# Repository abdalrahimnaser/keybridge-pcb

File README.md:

Get yourself a premade KeyBridge here: https://localdevices.net/products/keybridge

Link to the software repo: https://github.com/abdalrahimnaser/keybridge-esphome

## License
This hardware design is licensed under [CC BY-NC-SA 4.0](https://creativecommons.org/licenses/by-nc-sa/4.0/). 
You are free to build and modify it for personal, non-commercial use. Commercial manufacturing and sales are prohibited without prior written permission.

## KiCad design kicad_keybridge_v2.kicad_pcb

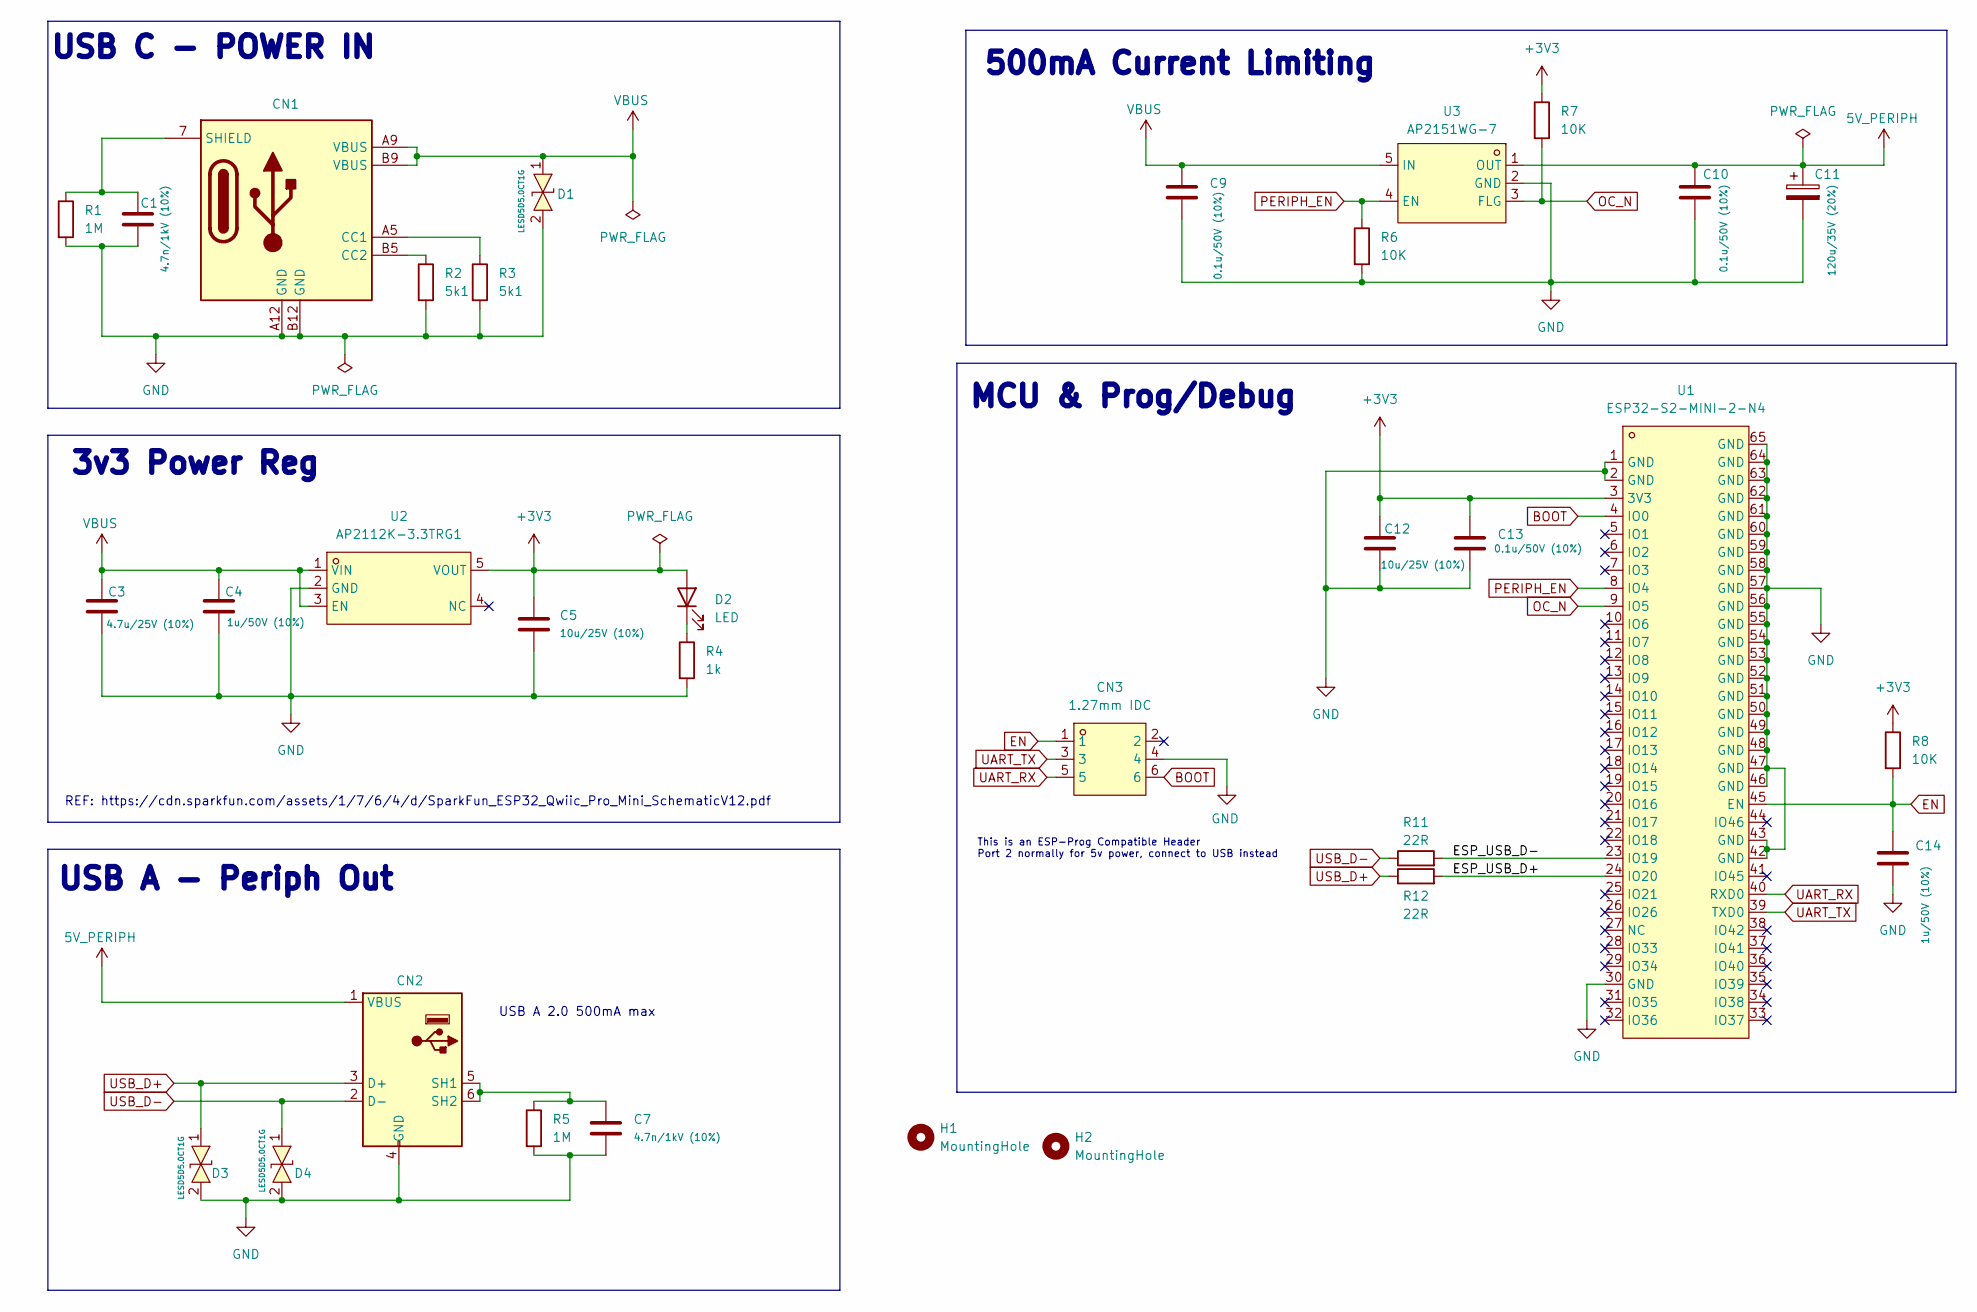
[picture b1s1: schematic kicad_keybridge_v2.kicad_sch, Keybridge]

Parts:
C1, C7: 4.7n/1kV (10%); C_1206_3216Metric; LCSC C107198
C3: 4.7u/25V (10%); C_0805_2012Metric; LCSC C98195
C4, C14: 1u/50V (10%); C_0805_2012Metric; LCSC C28323
C5, C12: 10u/25V (10%); C_0805_2012Metric; LCSC C15850
C9, C10, C13: 0.1u/50V (10%); C_0805_2012Metric; LCSC C1711
C11: 120u/35V (20%); CP_Elec_6.3x7.7; LCSC C49256854
CN1: USB-TYPE-C-6P_Power; TYPE-C-SMD_TYPE-C-6P; MPN USB-TYPE-C-009; LCSC Part C2927029
CN2: AF180QT1.0; USB-A-SMD_AF180QT1.0; MPN AF180QT1.0; LCSC Part C404963
CN3: 1.27mm IDC; CONN-SMD_6P-P1.27-LS5.8; MPN HX JN1.27-2x3 TP H4.9; LCSC Part C42372553
D1, D3, D4: LESD5D5.0CT1G; SOD-523_L1.2-W0.8-LS1.6-BI; MPN LESD5D5.0CT1G; LCSC Part C5246195
D2: LED; LED_0805_2012Metric_Pad1.15x1.40mm_HandSolder; LCSC C2297
H1, H2: MountingHole; MountingHole_2.2mm_M2
R1, R5: 1M; R_0603_1608Metric_Pad0.98x0.95mm_HandSolder; LCSC C2907003
R2, R3: 5k1; R_0603_1608Metric_Pad0.98x0.95mm_HandSolder; LCSC C2907044
R4: 1k; R_0603_1608Metric_Pad0.98x0.95mm_HandSolder; LCSC C2907002
R6, R7, R8: 10K; R_0603_1608Metric_Pad0.98x0.95mm_HandSolder; LCSC C844918
R11, R12: 22R; R_0603_1608Metric_Pad0.98x0.95mm_HandSolder; LCSC C107701
U1: ESP32-S2-MINI-2-N4; WIFI-SMD_ESP32-MINI-1-N4; MPN ESP32-S2-MINI-2-N4; LCSC Part C3013906
U2: AP2112K-3.3TRG1; SOT-25-5_L2.9-W1.6-P0.95-LS2.8-BL; MPN AP2112K-3.3TRG1; LCSC Part C51118
U3: AP2151WG-7; SOT-25-5_L3.0-W1.8-P0.95-LS3.0-BR; MPN AP2151WG-7; LCSC Part C110464

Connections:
5V_PERIPH: C10.1, C11.1, CN2.1 (VBUS), U3.1 (OUT)
+3V3: C5.1, C12.1, C13.1, D2.2 (A), R7.1, R8.1, U1.3 (3V3), U2.5 (VOUT)
/ESP_USB_D+: R12.2, U1.24 (IO20)
/ESP_USB_D-: R11.2, U1.23 (IO19)
BOOT: CN3.6, U1.4 (IO0)
EN: C14.1, CN3.1, R8.2, U1.45 (EN)
GND: C1.2, C3.2, C4.2, C5.2, C7.2, C9.2, C10.2, C11.2, C12.2, C13.2, C14.2, CN1.A12 (GND), CN1.B12 (GND), CN2.4 (GND), CN3.4, D1.2, D3.2, D4.2, R1.2, R2.2, R3.2, R4.2, R5.2, R6.2, U1.1 (GND), U1.2 (GND), U1.30 (GND), U1.42 (GND), U1.43 (GND), U1.46 (GND), U1.47 (GND), U1.48 (GND), U1.49 (GND), U1.50 (GND), U1.51 (GND), U1.52 (GND), U1.53 (GND), U1.54 (GND), U1.55 (GND), U1.56 (GND), U1.57 (GND), U1.58 (GND), U1.59 (GND), U1.60 (GND), U1.61 (GND), U1.62 (GND), U1.63 (GND), U1.64 (GND), U1.65 (GND), U2.2 (GND), U3.2 (GND)
unnamed: CN1.A5 (CC1), R3.1
unnamed: CN1.B5 (CC2), R2.1
unnamed: C1.1, CN1.7 (SHIELD), R1.1
unnamed: C7.1, CN2.5 (SH1), CN2.6 (SH2), R5.1
unnamed: D2.1 (K), R4.1
OC_N: R7.2, U1.9 (IO5), U3.3 (FLG)
PERIPH_EN: R6.1, U1.8 (IO4), U3.4 (EN)
UART_RX: CN3.5, U1.40 (RXD0)
UART_TX: CN3.3, U1.39 (TXD0)
USB_D+: CN2.3 (D+), D3.1, R12.1
USB_D-: CN2.2 (D-), D4.1, R11.1
VBUS: C3.1, C4.1, C9.1, CN1.A9 (VBUS), CN1.B9 (VBUS), D1.1, U2.1 (VIN), U2.3 (EN), U3.5 (IN)

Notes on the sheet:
3v3 Power Reg
REF: https://cdn.sparkfun.com/assets/1/7/6/4/d/SparkFun_ESP32_Qwiic_Pro_Mini_SchematicV12.pdf
USB A 2.0 500mA max
USB A - Periph Out
This is an ESP-Prog Compatible Header Port 2 normally for 5v power, connect to USB instead
MCU & Prog/Debug
USB C - POWER IN
500mA Current Limiting

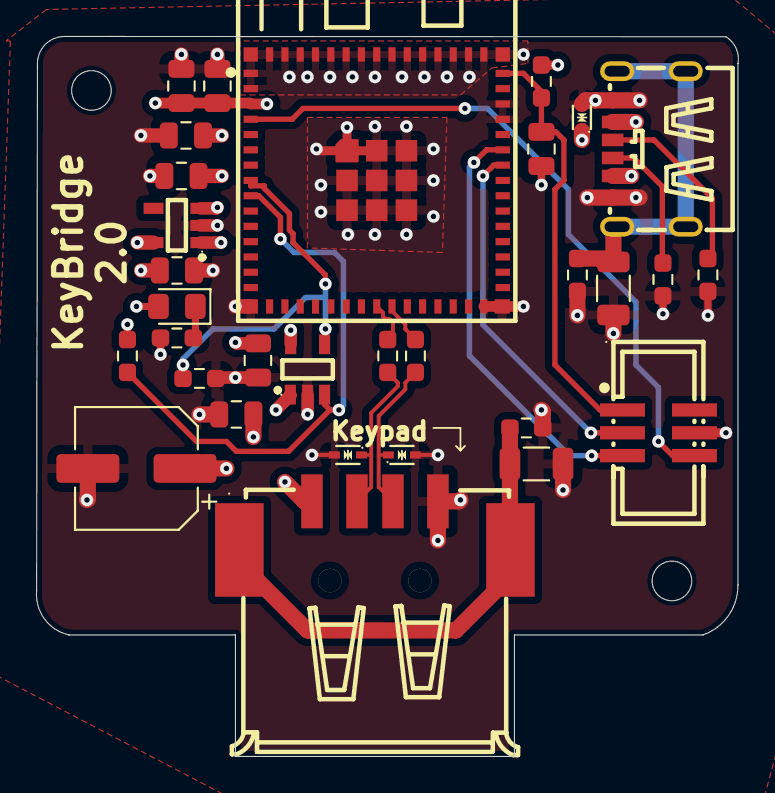
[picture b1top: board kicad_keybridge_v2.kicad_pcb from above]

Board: 4 copper layers, 39.0 x 40.0 mm, 33 parts (0 on the bottom side), 19 nets.
